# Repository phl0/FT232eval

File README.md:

# FT232eval
FT232RL Evaluation Board with CBUS I/O

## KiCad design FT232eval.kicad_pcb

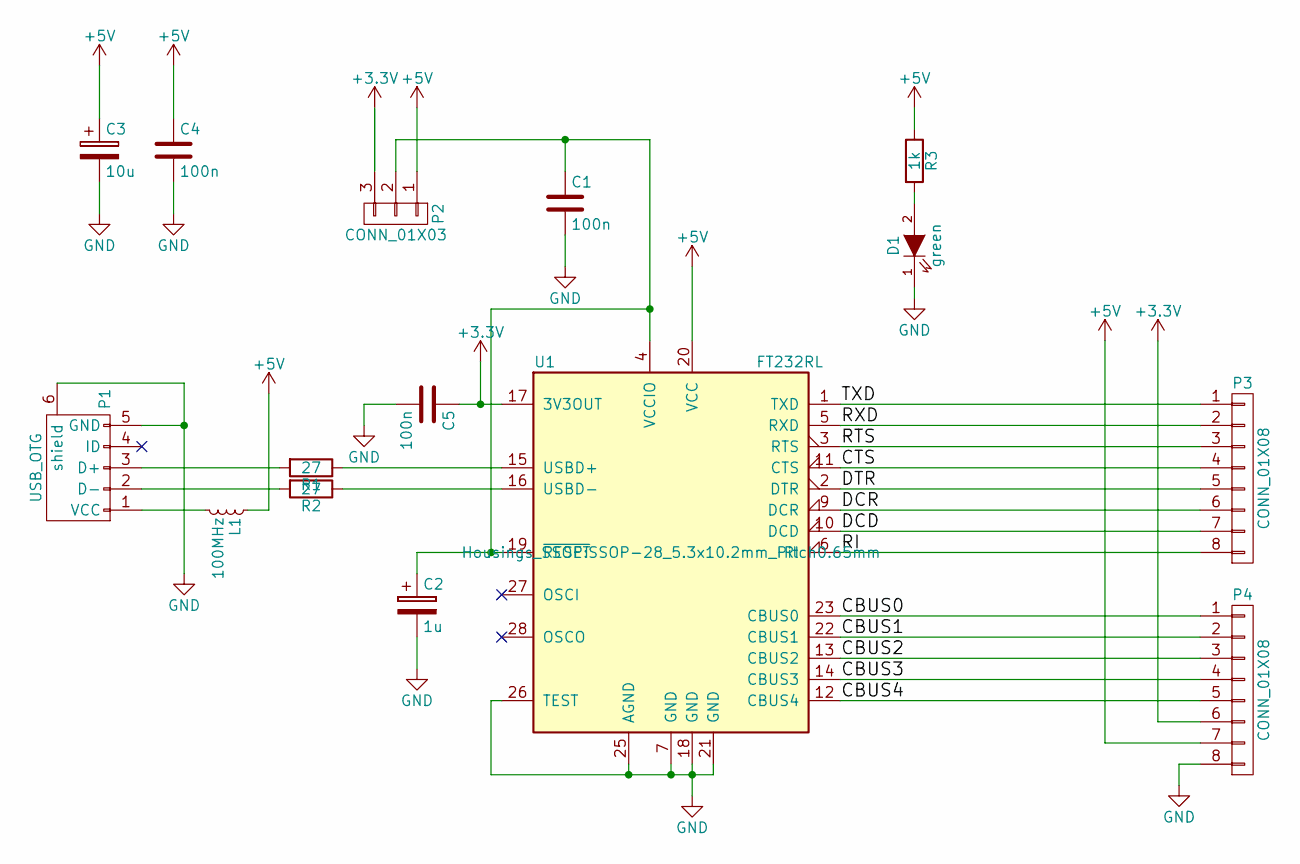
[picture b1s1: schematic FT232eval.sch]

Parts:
C1, C4, C5: 100n; C_0603_HandSoldering
C2: 1u; c_elec_4x5.7
C3: 10u; c_elec_4x5.7
D1: green; LED_0603
L1: 100MHz; R_0603_HandSoldering
P1: USB_OTG; USB_Mini-B
P2: CONN_01X03; Pin_Header_Straight_1x03
P3, P4: CONN_01X08; Pin_Header_Straight_1x08
R1, R2: 27; R_0603_HandSoldering
R3: 1k; R_0603_HandSoldering
U1: FT232RL; SSOP-28_5.3x10.2mm_Pitch0.65mm

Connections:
+3V3: C5.1, P2.3, P4.6, U1.17 (3V3OUT)
+5V: C3.1, C4.1, L1.1, P2.1, P4.7, R3.1, U1.20 (VCC)
/CBUS0: P4.1, U1.23 (CBUS0)
/CBUS1: P4.2, U1.22 (CBUS1)
/CBUS2: P4.3, U1.13 (CBUS2)
/CBUS3: P4.4, U1.14 (CBUS3)
/CBUS4: P4.5, U1.12 (CBUS4)
/CTS: P3.4, U1.11 (CTS)
/DCD: P3.7, U1.10 (DCD)
/DCR: P3.6, U1.9 (DCR)
/DTR: P3.5, U1.2 (DTR)
/RI: P3.8, U1.6 (RI)
/RTS: P3.3, U1.3 (RTS)
/RXD: P3.2, U1.5 (RXD)
/TXD: P3.1, U1.1 (TXD)
GND: C1.2, C2.2, C3.2, C4.2, C5.2, D1.1 (K), P1.5 (GND), P1.6 (shield), P4.8, U1.7 (GND), U1.18 (GND), U1.21 (GND), U1.25 (AGND), U1.26 (TEST)
unnamed: C1.1, C2.1, P2.2, U1.4 (VCCIO), U1.19 (~RESET~)
unnamed: D1.2 (A), R3.2
unnamed: L1.2, P1.1 (VCC)
unnamed: P1.2 (D-), R2.2
unnamed: P1.3 (D+), R1.2
unnamed: R1.1, U1.15 (USBD+)
unnamed: R2.1, U1.16 (USBD-)

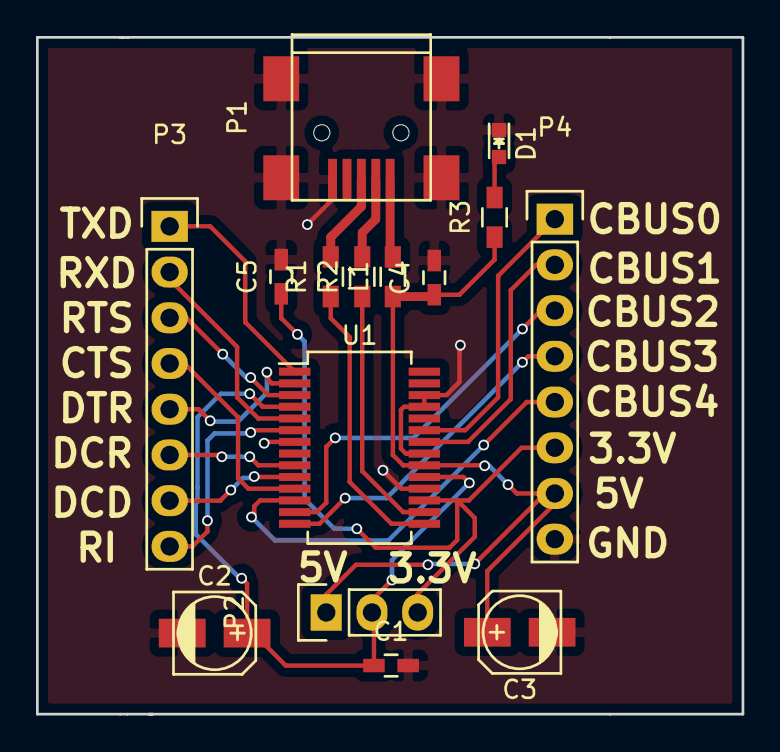
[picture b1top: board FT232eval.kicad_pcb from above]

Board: 2 copper layers, 39.2 x 37.6 mm, 15 parts (0 on the bottom side), 23 nets.

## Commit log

2017-08-20 Add first draft.
2017-08-21 Add board layout and gerber files
2017-08-21 Rename Edge Cuts
2017-08-21 Add dimensions
